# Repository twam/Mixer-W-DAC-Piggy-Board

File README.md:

Mixer-W-DAC-Piggy-Board
===

This repository is part of the USB audio mixer project described on https://www.twam.info/general/building-a-custom-usb-audio-mixer.

## License

[![CC BY-SA 4.0][cc-by-sa-shield]][cc-by-sa]

This work is licensed under a [Creative Commons Attribution-NonCommercial-ShareAlike 4.0 International License][cc-by-sa].

[![CC BY-SA 4.0][cc-by-sa-image]][cc-by-sa]

[cc-by-sa]: http://creativecommons.org/licenses/by-nc-sa/4.0/
[cc-by-sa-image]: https://licensebuttons.net/l/by-nc-sa/4.0/88x31.png
[cc-by-sa-shield]: https://img.shields.io/badge/License-CC%20BY--NC--SA%204.0-lightgrey.svg

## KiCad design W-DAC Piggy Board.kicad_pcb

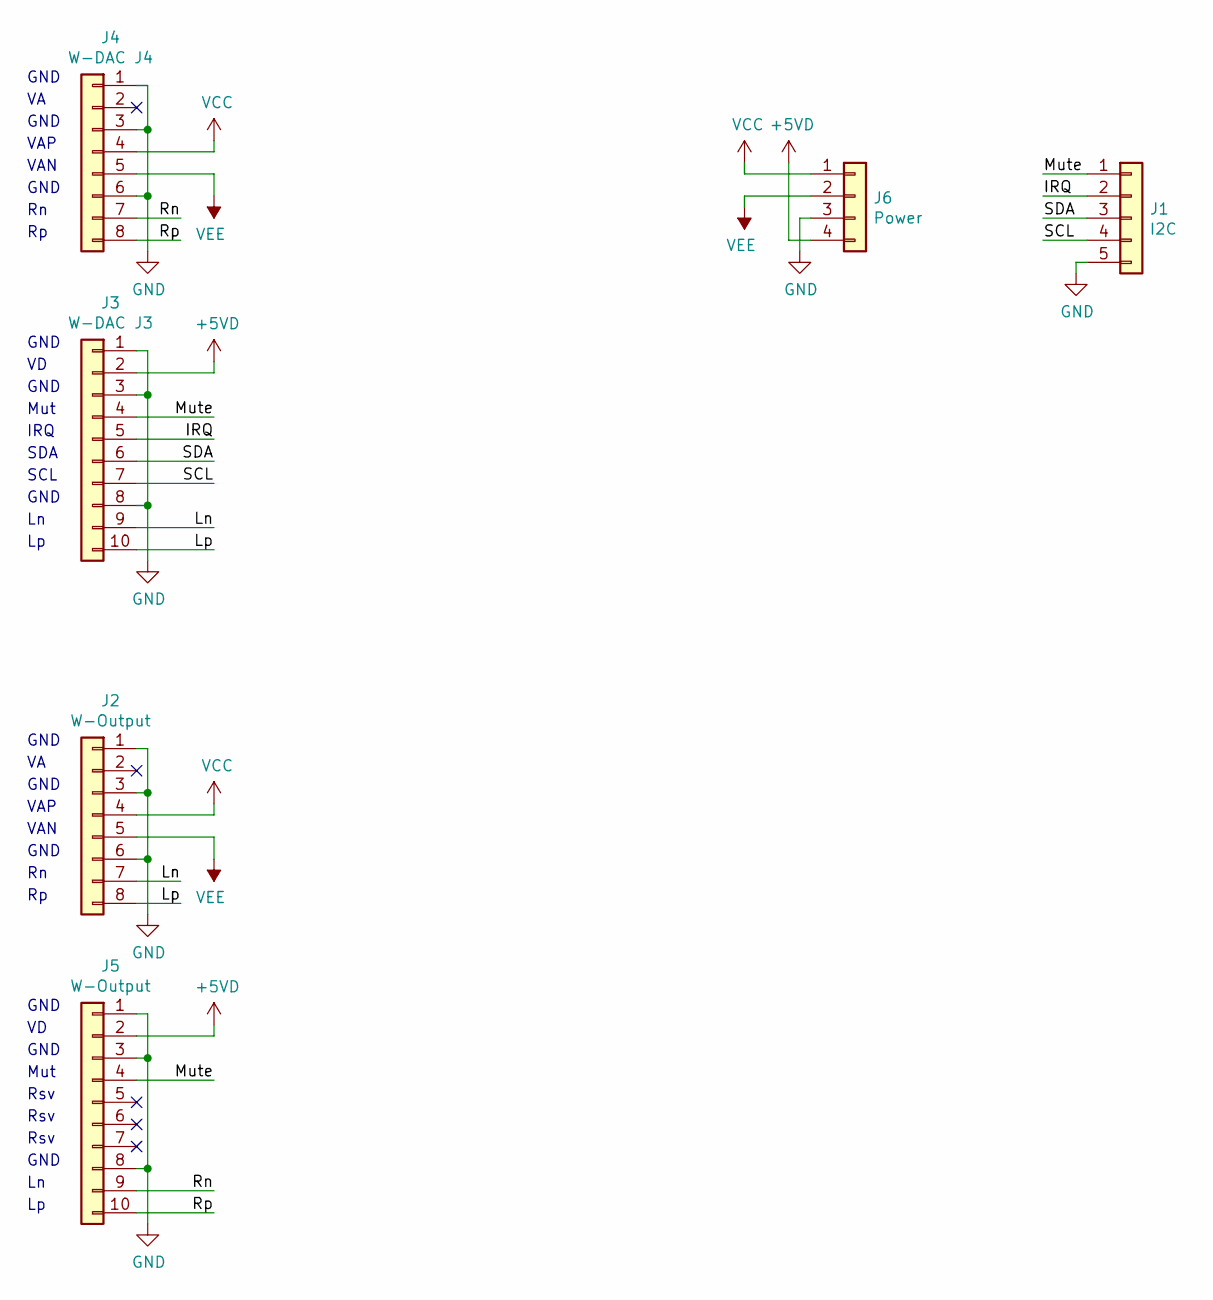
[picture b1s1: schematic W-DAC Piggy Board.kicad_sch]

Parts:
J1: I2C; PinHeader_1x05_P2.54mm_Horizontal
J2: W-Output; PinSocket_1x08_P2.54mm_Vertical
J3: W-DAC J3; PinSocket_1x10_P2.54mm_Vertical
J4: W-DAC J4; PinSocket_1x08_P2.54mm_Vertical
J5: W-Output; PinSocket_1x10_P2.54mm_Vertical
J6: Power; JST_VH_B4PS-VH_1x04_P3.96mm_Horizontal

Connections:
+5VD: J3.2, J5.2, J6.4
/IRQ: J1.2, J3.5
/Ln: J2.7, J3.9
/Lp: J2.8, J3.10
/Mute: J1.1, J3.4, J5.4
/Rn: J4.7, J5.9
/Rp: J4.8, J5.10
/SCL: J1.4, J3.7
/SDA: J1.3, J3.6
GND: J1.5, J2.1, J2.3, J2.6, J3.1, J3.3, J3.8, J4.1, J4.3, J4.6, J5.1, J5.3, J5.8, J6.3
VCC: J2.4, J4.4, J6.1
VEE: J2.5, J4.5, J6.2

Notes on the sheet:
GND
VAN
Rsv
Mut
IRQ
VAP
SCL
SDA

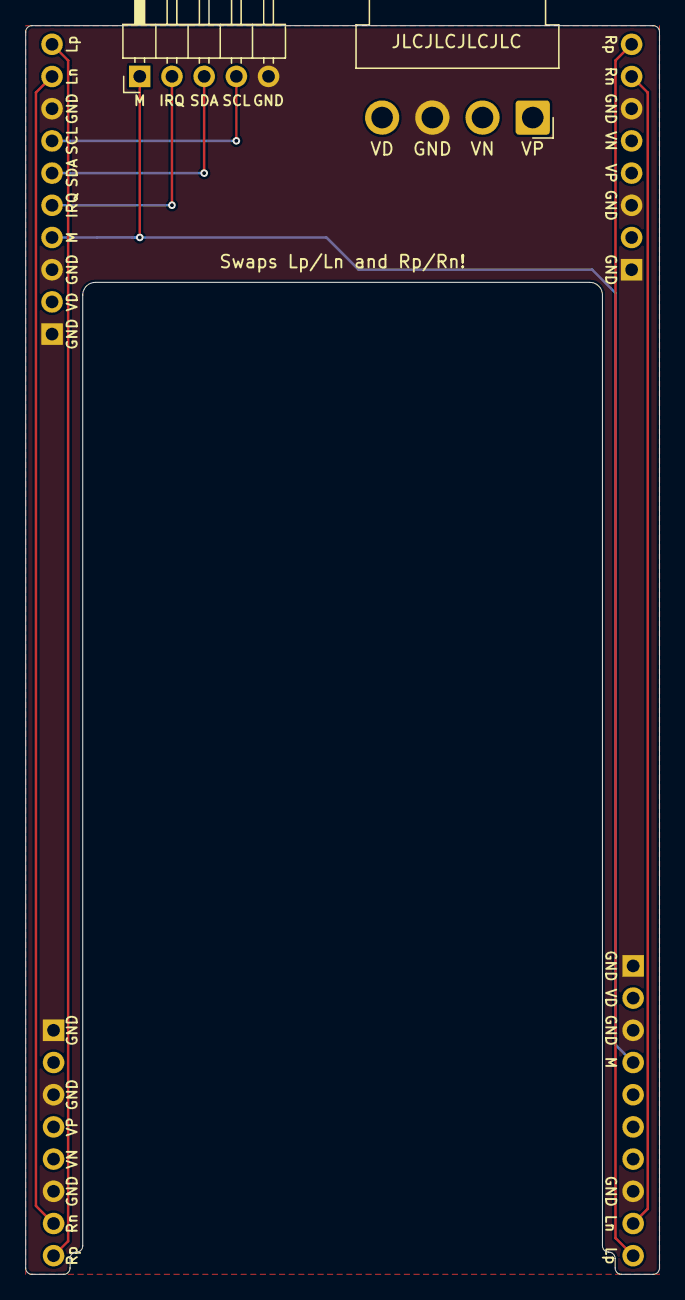
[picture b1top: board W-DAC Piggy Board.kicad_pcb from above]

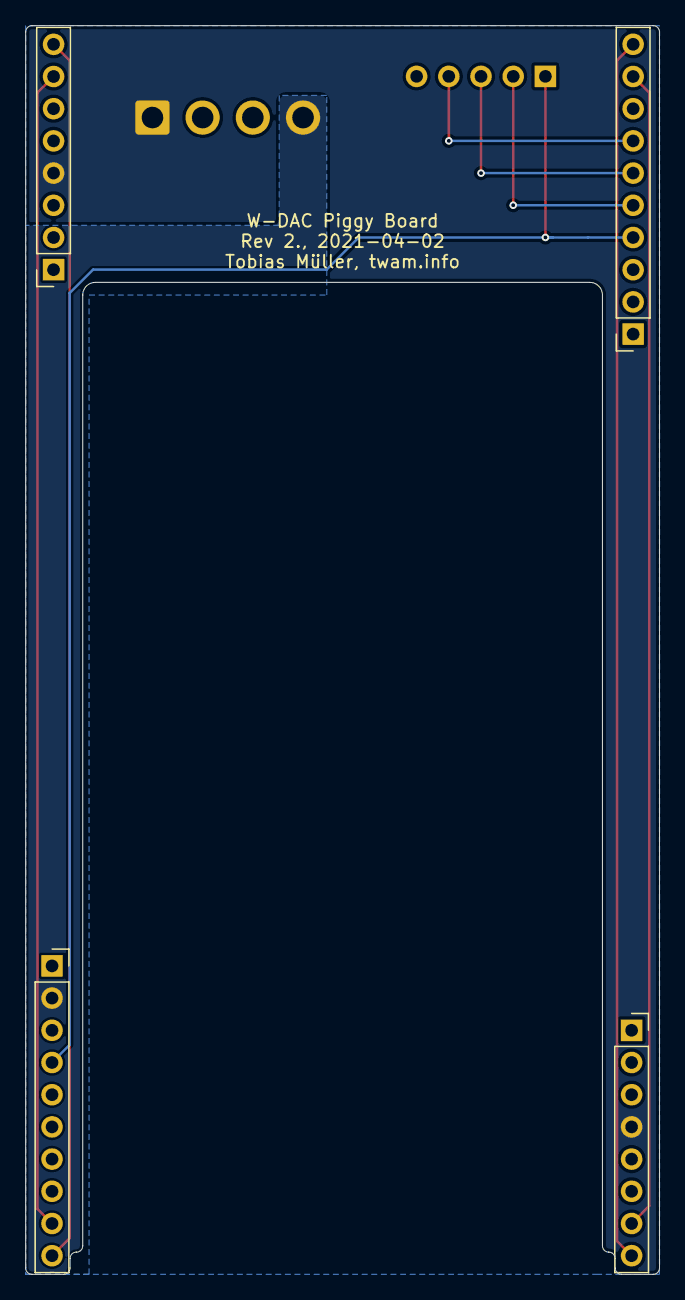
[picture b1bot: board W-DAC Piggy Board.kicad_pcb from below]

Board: 4 copper layers, 50.0 x 98.5 mm, 6 parts (4 on the bottom side), 12 nets.

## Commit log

2022-01-07 Update to KiCad 6
2022-01-15 Add README
